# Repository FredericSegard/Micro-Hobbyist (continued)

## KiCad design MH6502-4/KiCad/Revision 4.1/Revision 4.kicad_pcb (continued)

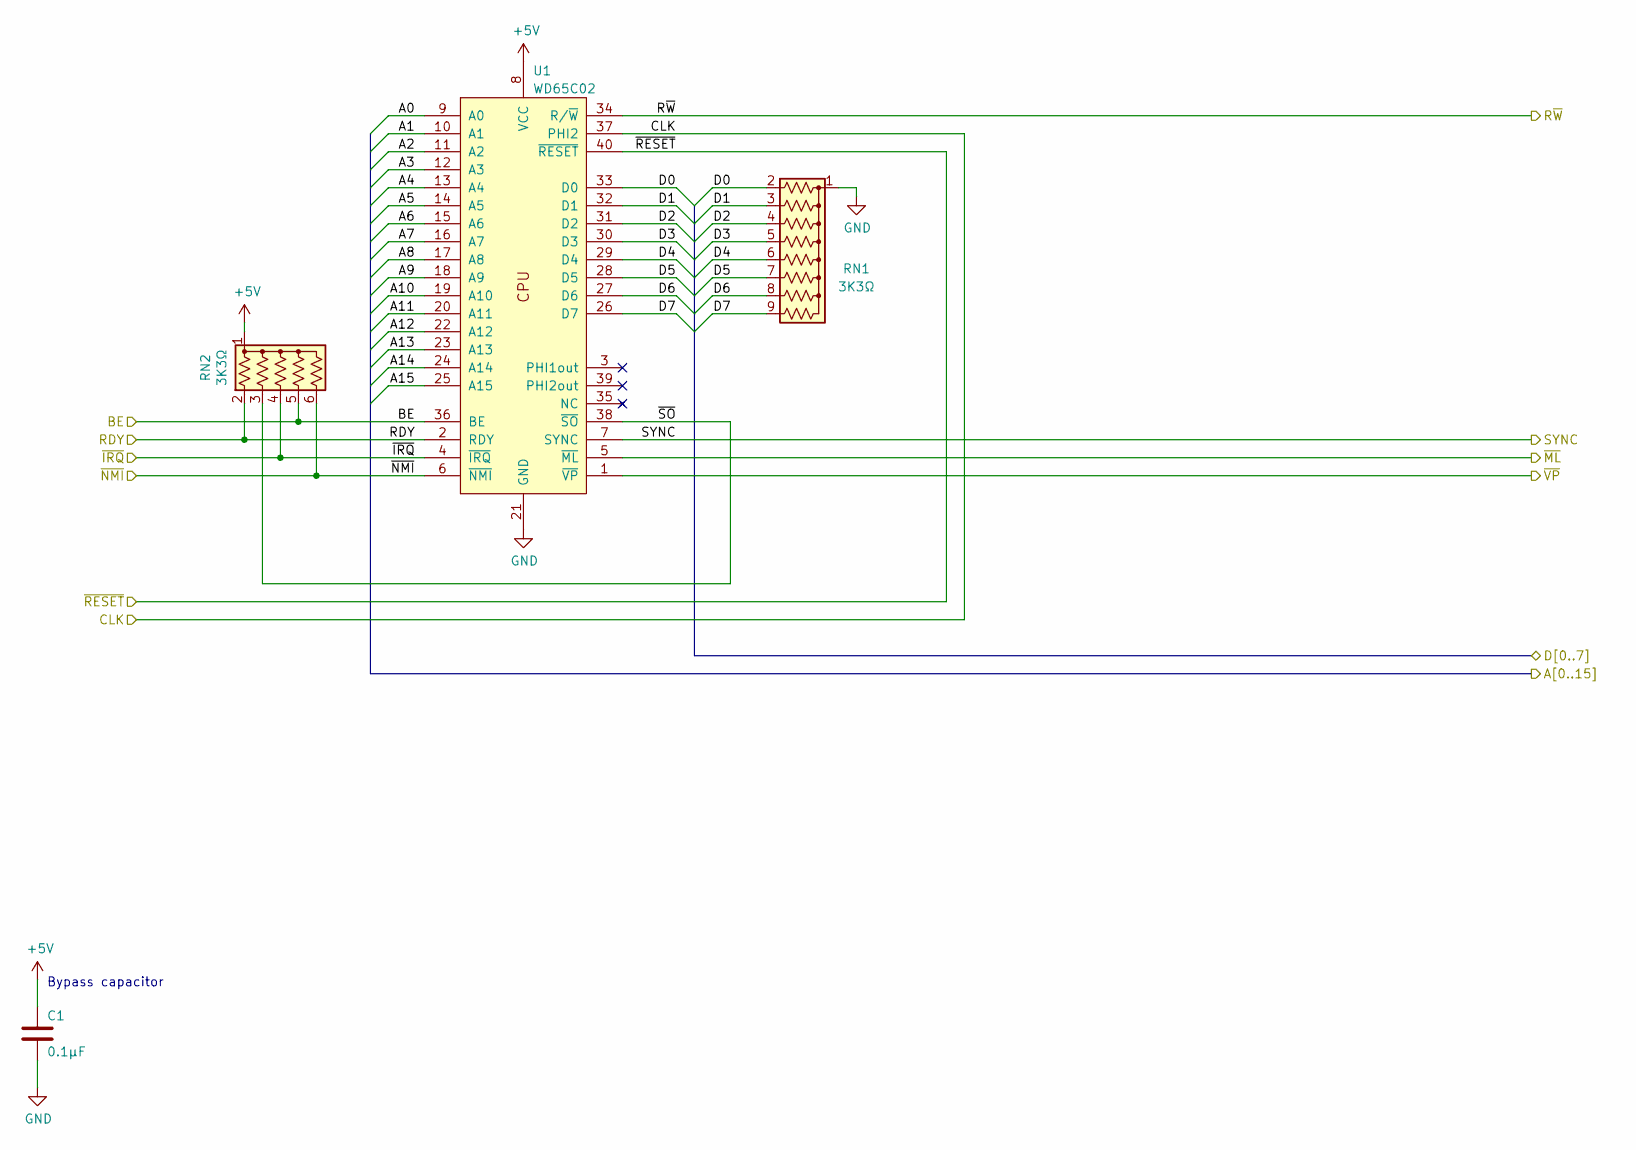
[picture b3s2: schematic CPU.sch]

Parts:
C1: 0.1µF; C_Disc_D3.0mm_W1.6mm_P2.50mm
RN1: 3K3Ω; R_Array_SIP9
RN2: 3K3Ω; R_Array_SIP6
U1: WD65C02; DIP-40_W15.24mm_Socket

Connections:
+5V: C1.1, RN2.1 (common), U1.8 (VCC); also elsewhere on the board
/ACIA/A0: U1.9 (A0); also elsewhere on the board
/ACIA/A1: U1.10 (A1); also elsewhere on the board
/ACIA/D0: RN1.2 (R1), U1.33 (D0); also elsewhere on the board
/ACIA/D1: RN1.3 (R2), U1.32 (D1); also elsewhere on the board
/ACIA/D2: RN1.4 (R3), U1.31 (D2); also elsewhere on the board
/ACIA/D3: RN1.5 (R4), U1.30 (D3); also elsewhere on the board
/ACIA/D4: RN1.6 (R5), U1.29 (D4); also elsewhere on the board
/ACIA/D5: RN1.7 (R6), U1.28 (D5); also elsewhere on the board
/ACIA/D6: RN1.8 (R7), U1.27 (D6); also elsewhere on the board
/ACIA/D7: RN1.9 (R8), U1.26 (D7); also elsewhere on the board
/BE: RN2.5 (R4), U1.36 (BE); also elsewhere on the board
/Bus/A2: U1.11 (A2); also elsewhere on the board
/Bus/A3: U1.12 (A3); also elsewhere on the board
/Bus/A4: U1.13 (A4); also elsewhere on the board
/Bus/A5: U1.14 (A5); also elsewhere on the board
/Bus/A6: U1.15 (A6); also elsewhere on the board
/Bus/A7: U1.16 (A7); also elsewhere on the board
/CLK: U1.37 (PHI2); also elsewhere on the board
/CPU/A8: U1.17 (A8); also elsewhere on the board
/CPU/A9: U1.18 (A9); also elsewhere on the board
/CPU/A10: U1.19 (A10); also elsewhere on the board
/CPU/A11: U1.20 (A11); also elsewhere on the board
/CPU/A12: U1.22 (A12); also elsewhere on the board
/CPU/A13: U1.23 (A13); also elsewhere on the board
/CPU/A14: U1.24 (A14); also elsewhere on the board
/CPU/A15: U1.25 (A15); also elsewhere on the board
/CPU/~SO: RN2.3 (R2), U1.38 (~SO)
/RDY: RN2.2 (R1), U1.2 (RDY); also elsewhere on the board
/R~W: U1.34 (R/~W); also elsewhere on the board
/SYNC: U1.7 (SYNC); also elsewhere on the board
/~IRQ: RN2.4 (R3), U1.4 (~IRQ); also elsewhere on the board
/~ML: U1.5 (~ML); also elsewhere on the board
/~NMI: RN2.6 (R5), U1.6 (~NMI); also elsewhere on the board
/~RESET: U1.40 (~RESET); also elsewhere on the board
/~VP: U1.1 (~VP); also elsewhere on the board
GND: C1.2, RN1.1 (common), U1.21 (GND); also elsewhere on the board

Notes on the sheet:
Bypass capacitor

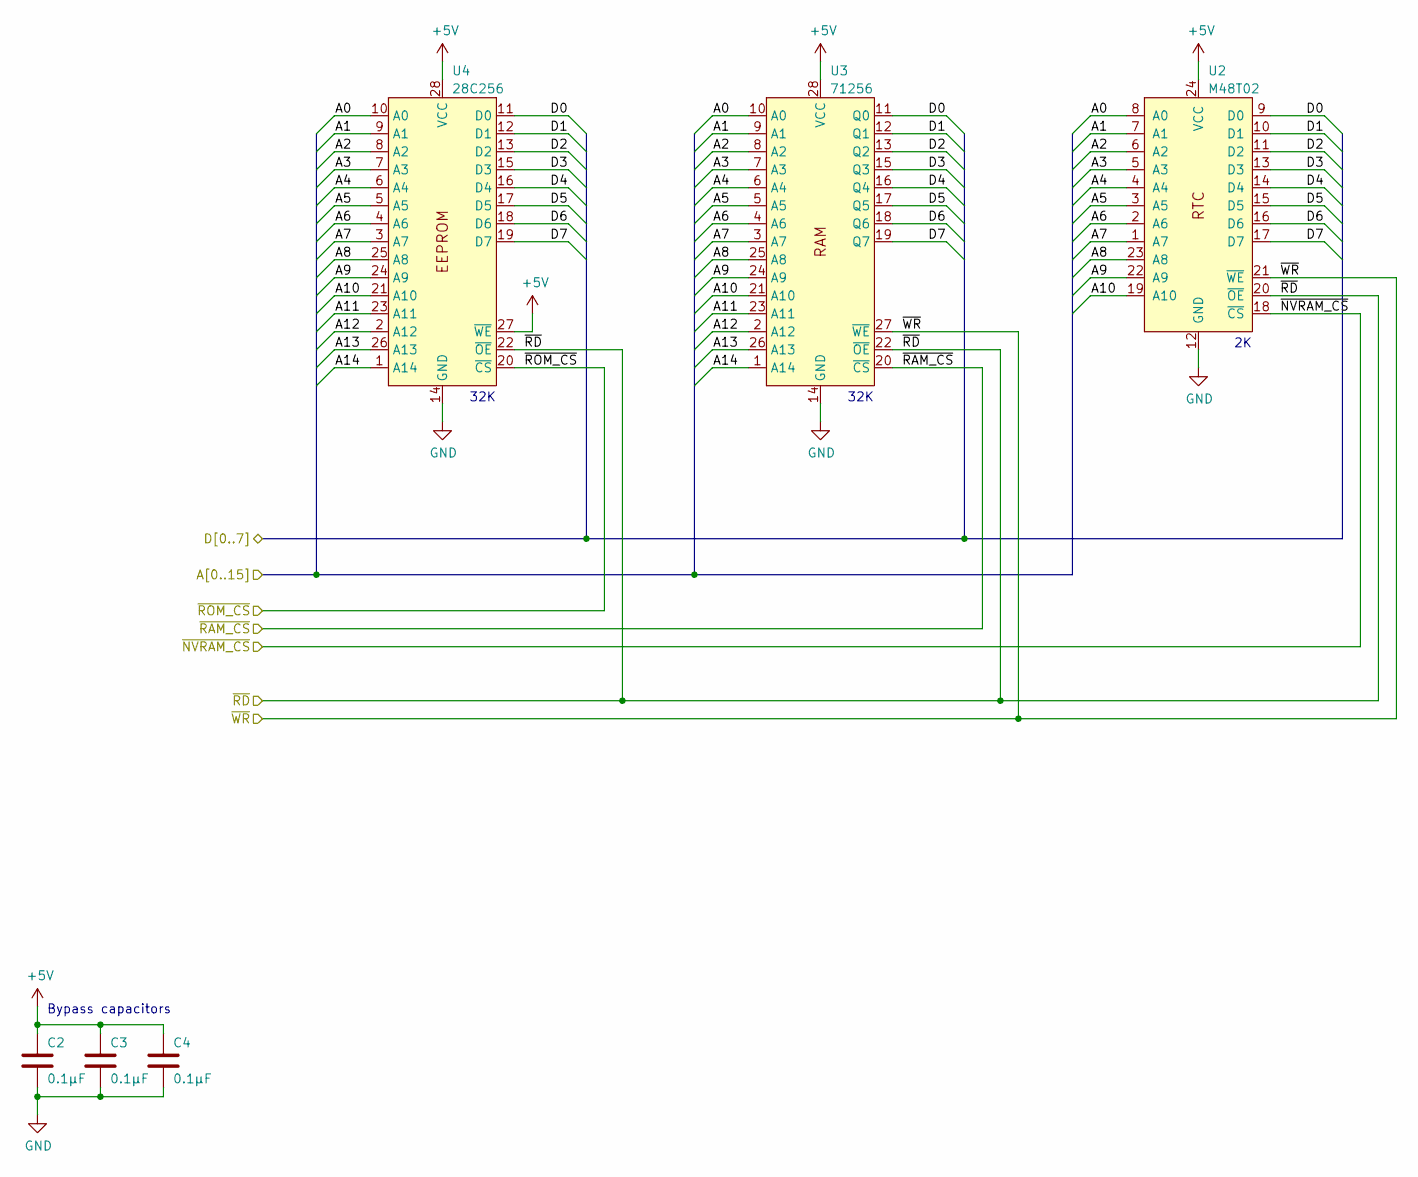
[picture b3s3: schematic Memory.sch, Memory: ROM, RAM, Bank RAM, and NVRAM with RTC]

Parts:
C2, C3, C4: 0.1µF; C_Disc_D3.0mm_W1.6mm_P2.50mm
U2: M48T02; DIP-24_W15.24mm_Socket
U3: 71256; DIP-28_W7.62mm_Socket
U4: 28C256; ZIF-28

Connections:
+5V: C2.1, C3.1, C4.1, U2.24 (VCC), U3.28 (VCC), U4.27 (~WE), U4.28 (VCC); also elsewhere on the board
/ACIA/A0: U2.8 (A0), U3.10 (A0), U4.10 (A0); also elsewhere on the board
/ACIA/A1: U2.7 (A1), U3.9 (A1), U4.9 (A1); also elsewhere on the board
/ACIA/D0: U2.9 (D0), U3.11 (Q0), U4.11 (D0); also elsewhere on the board
/ACIA/D1: U2.10 (D1), U3.12 (Q1), U4.12 (D1); also elsewhere on the board
/ACIA/D2: U2.11 (D2), U3.13 (Q2), U4.13 (D2); also elsewhere on the board
/ACIA/D3: U2.13 (D3), U3.15 (Q3), U4.15 (D3); also elsewhere on the board
/ACIA/D4: U2.14 (D4), U3.16 (Q4), U4.16 (D4); also elsewhere on the board
/ACIA/D5: U2.15 (D5), U3.17 (Q5), U4.17 (D5); also elsewhere on the board
/ACIA/D6: U2.16 (D6), U3.18 (Q6), U4.18 (D6); also elsewhere on the board
/ACIA/D7: U2.17 (D7), U3.19 (Q7), U4.19 (D7); also elsewhere on the board
/Bus/A2: U2.6 (A2), U3.8 (A2), U4.8 (A2); also elsewhere on the board
/Bus/A3: U2.5 (A3), U3.7 (A3), U4.7 (A3); also elsewhere on the board
/Bus/A4: U2.4 (A4), U3.6 (A4), U4.6 (A4); also elsewhere on the board
/Bus/A5: U2.3 (A5), U3.5 (A5), U4.5 (A5); also elsewhere on the board
/Bus/A6: U2.2 (A6), U3.4 (A6), U4.4 (A6); also elsewhere on the board
/Bus/A7: U2.1 (A7), U3.3 (A7), U4.3 (A7); also elsewhere on the board
/CPU/A8: U2.23 (A8), U3.25 (A8), U4.25 (A8); also elsewhere on the board
/CPU/A9: U2.22 (A9), U3.24 (A9), U4.24 (A9); also elsewhere on the board
/CPU/A10: U2.19 (A10), U3.21 (A10), U4.21 (A10); also elsewhere on the board
/CPU/A11: U3.23 (A11), U4.23 (A11); also elsewhere on the board
/CPU/A12: U3.2 (A12), U4.2 (A12); also elsewhere on the board
/CPU/A13: U3.26 (A13), U4.26 (A13); also elsewhere on the board
/CPU/A14: U3.1 (A14), U4.1 (A14); also elsewhere on the board
/~NVRAM: U2.18 (~CS); also elsewhere on the board
/~RAM: U3.20 (~CS); also elsewhere on the board
/~RD: U2.20 (~OE), U3.22 (~OE), U4.22 (~OE); also elsewhere on the board
/~ROM: U4.20 (~CS); also elsewhere on the board
/~WR: U2.21 (~WE), U3.27 (~WE); also elsewhere on the board
GND: C2.2, C3.2, C4.2, U2.12 (GND), U3.14 (GND), U4.14 (GND); also elsewhere on the board

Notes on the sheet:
32K
Bypass capacitors

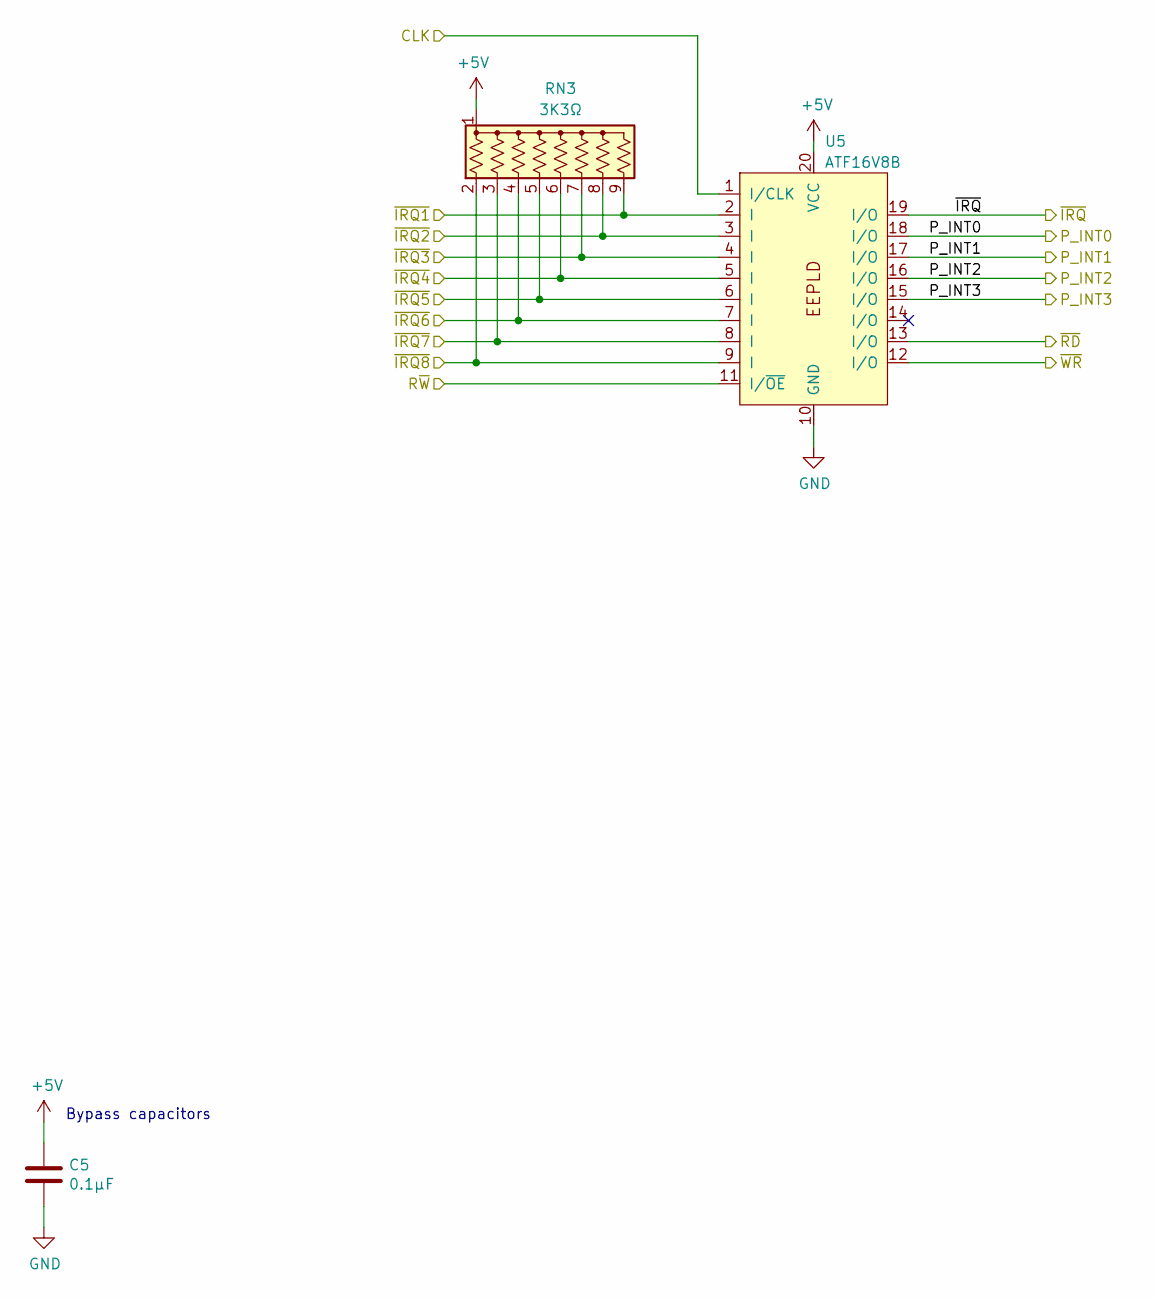
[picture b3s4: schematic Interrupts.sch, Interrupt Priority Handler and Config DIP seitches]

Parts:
C5: 0.1µF; C_Disc_D3.0mm_W1.6mm_P2.50mm
RN3: 3K3Ω; R_Array_SIP9
U5: ATF16V8B; DIP-20_W7.62mm_Socket

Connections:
+5V: C5.1, RN3.1 (common), U5.20 (VCC); also elsewhere on the board
/CLK: U5.1 (I/CLK); also elsewhere on the board
/P_INT0: U5.18 (I/O); also elsewhere on the board
/P_INT1: U5.17 (I/O); also elsewhere on the board
/P_INT2: U5.16 (I/O); also elsewhere on the board
/P_INT3: U5.15 (I/O); also elsewhere on the board
/R~W: U5.11 (I/~OE); also elsewhere on the board
/~IRQ: U5.19 (I/O); also elsewhere on the board
/~IRQ1: RN3.9 (R8), U5.2 (I); also elsewhere on the board
/~IRQ2: RN3.8 (R7), U5.3 (I); also elsewhere on the board
/~IRQ3: RN3.7 (R6), U5.4 (I); also elsewhere on the board
/~IRQ4: RN3.6 (R5), U5.5 (I); also elsewhere on the board
/~IRQ5: RN3.5 (R4), U5.6 (I); also elsewhere on the board
/~IRQ6: RN3.4 (R3), U5.7 (I); also elsewhere on the board
/~IRQ7: RN3.3 (R2), U5.8 (I); also elsewhere on the board
/~IRQ8: RN3.2 (R1), U5.9 (I)
/~RD: U5.13 (I/O); also elsewhere on the board
/~WR: U5.12 (I/O); also elsewhere on the board
GND: C5.2, U5.10 (GND); also elsewhere on the board

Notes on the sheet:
Bypass capacitors

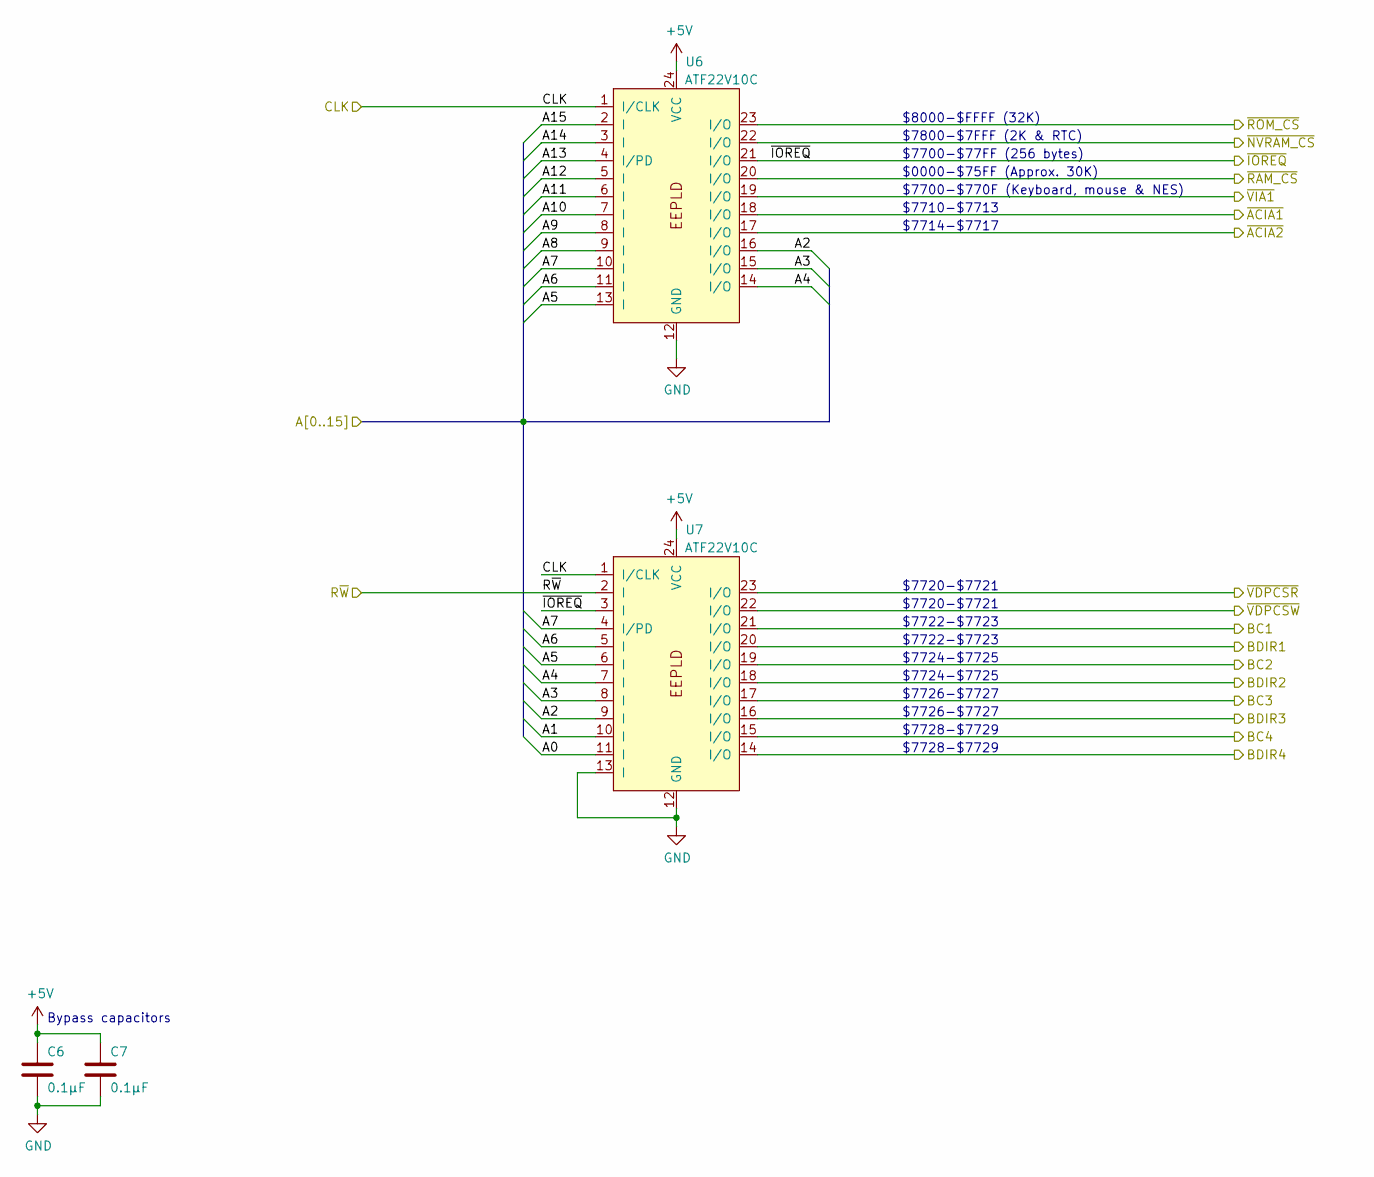
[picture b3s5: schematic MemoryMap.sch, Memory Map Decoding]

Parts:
C6, C7: 0.1µF; C_Disc_D3.0mm_W1.6mm_P2.50mm
U6, U7: ATF22V10C; DIP-24_W7.62mm_Socket

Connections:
+5V: C6.1, C7.1, U6.24 (VCC), U7.24 (VCC); also elsewhere on the board
/ACIA/A0: U7.11 (I); also elsewhere on the board
/ACIA/A1: U7.10 (I); also elsewhere on the board
/BC1: U7.21 (I/O); also elsewhere on the board
/BC2: U7.19 (I/O); also elsewhere on the board
/BC3: U7.17 (I/O); also elsewhere on the board
/BC4: U7.15 (I/O); also elsewhere on the board
/BDIR1: U7.20 (I/O); also elsewhere on the board
/BDIR2: U7.18 (I/O); also elsewhere on the board
/BDIR3: U7.16 (I/O); also elsewhere on the board
/BDIR4: U7.14 (I/O); also elsewhere on the board
/Bus/A2: U6.16 (I/O), U7.9 (I); also elsewhere on the board
/Bus/A3: U6.15 (I/O), U7.8 (I); also elsewhere on the board
/Bus/A4: U6.14 (I/O), U7.7 (I); also elsewhere on the board
/Bus/A5: U6.13 (I), U7.6 (I); also elsewhere on the board
/Bus/A6: U6.11 (I), U7.5 (I); also elsewhere on the board
/Bus/A7: U6.10 (I), U7.4 (I/PD); also elsewhere on the board
/CLK: U6.1 (I/CLK), U7.1 (I/CLK); also elsewhere on the board
/CPU/A8: U6.9 (I); also elsewhere on the board
/CPU/A9: U6.8 (I); also elsewhere on the board
/CPU/A10: U6.7 (I); also elsewhere on the board
/CPU/A11: U6.6 (I); also elsewhere on the board
/CPU/A12: U6.5 (I); also elsewhere on the board
/CPU/A13: U6.4 (I/PD); also elsewhere on the board
/CPU/A14: U6.3 (I); also elsewhere on the board
/CPU/A15: U6.2 (I); also elsewhere on the board
/R~W: U7.2 (I); also elsewhere on the board
/~ACIA1: U6.18 (I/O); also elsewhere on the board
/~ACIA2: U6.17 (I/O); also elsewhere on the board
/~IOREQ: U6.21 (I/O), U7.3 (I); also elsewhere on the board
/~NVRAM: U6.22 (I/O); also elsewhere on the board
/~RAM: U6.20 (I/O); also elsewhere on the board
/~ROM: U6.23 (I/O); also elsewhere on the board
/~VDPCSR: U7.23 (I/O); also elsewhere on the board
/~VDPCSW: U7.22 (I/O); also elsewhere on the board
/~VIA1: U6.19 (I/O); also elsewhere on the board
GND: C6.2, C7.2, U6.12 (GND), U7.12 (GND), U7.13 (I); also elsewhere on the board

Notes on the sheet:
Bypass capacitors
$8000-$FFFF (32K)
$7800-$7FFF (2K & RTC)
$7700-$77FF (256 bytes)
$0000-$75FF (Approx. 30K)
$7714-$7717
$7700-$770F (Keyboard, mouse & NES)
$7720-$7721
$7722-$7723
$7724-$7725
$7726-$7727
$7710-$7713
$7728-$7729

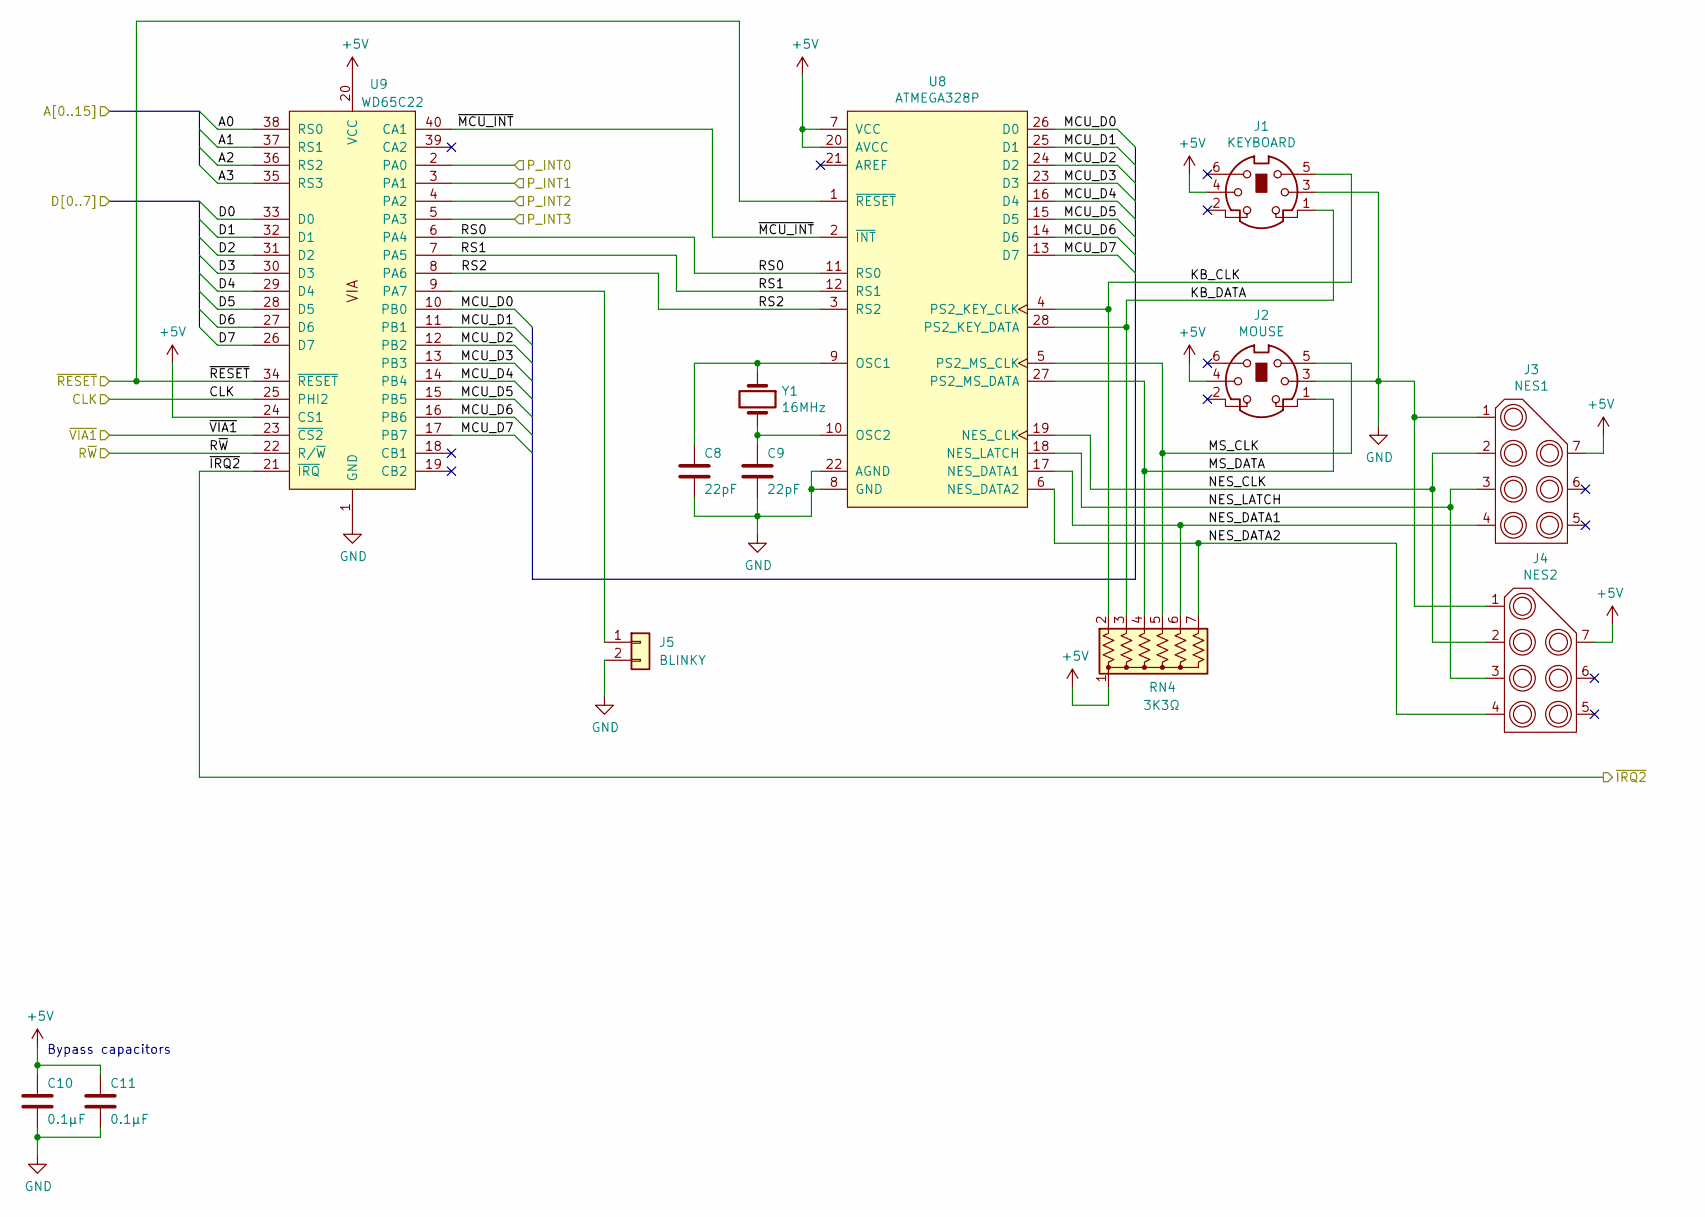
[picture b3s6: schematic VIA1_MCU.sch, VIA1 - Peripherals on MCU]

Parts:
C8, C9: 22pF; C_Disc_D3.0mm_W1.6mm_P2.50mm
C10, C11: 0.1µF; C_Disc_D3.0mm_W1.6mm_P2.50mm
J1: KEYBOARD; Mini-DIN_6p
J2: MOUSE; Mini-DIN_6p
J3: NES1; NES_Connector
J4: NES2; NES_Connector
J5: BLINKY; PinHeader_1x02_P2.54mm_Vertical
RN4: 3K3Ω; R_Array_SIP7
U8: ATMEGA328P; DIP-28_W7.62mm_Socket
U9: WD65C22; DIP-40_W15.24mm_Socket
Y1: 16MHz; Crystal_HC18-U_Vertical

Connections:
+5V: C10.1, C11.1, J1.4, J2.4, J3.7, J4.7, RN4.1 (common), U8.7 (VCC), U8.20 (AVCC), U9.20 (VCC), U9.24 (CS1); also elsewhere on the board
/ACIA/A0: U9.38 (RS0); also elsewhere on the board
/ACIA/A1: U9.37 (RS1); also elsewhere on the board
/ACIA/D0: U9.33 (D0); also elsewhere on the board
/ACIA/D1: U9.32 (D1); also elsewhere on the board
/ACIA/D2: U9.31 (D2); also elsewhere on the board
/ACIA/D3: U9.30 (D3); also elsewhere on the board
/ACIA/D4: U9.29 (D4); also elsewhere on the board
/ACIA/D5: U9.28 (D5); also elsewhere on the board
/ACIA/D6: U9.27 (D6); also elsewhere on the board
/ACIA/D7: U9.26 (D7); also elsewhere on the board
/Bus/A2: U9.36 (RS2); also elsewhere on the board
/Bus/A3: U9.35 (RS3); also elsewhere on the board
/CLK: U9.25 (PHI2); also elsewhere on the board
/P_INT0: U9.2 (PA0); also elsewhere on the board
/P_INT1: U9.3 (PA1); also elsewhere on the board
/P_INT2: U9.4 (PA2); also elsewhere on the board
/P_INT3: U9.5 (PA3); also elsewhere on the board
/R~W: U9.22 (R/~W); also elsewhere on the board
/VIA - Peripherals/KB_CLK: J1.5, RN4.2 (R1), U8.4 (PS2_KEY_CLK)
/VIA - Peripherals/KB_DATA: J1.1, RN4.3 (R2), U8.28 (PS2_KEY_DATA)
/VIA - Peripherals/MCU_D0: U8.26 (D0), U9.10 (PB0)
/VIA - Peripherals/MCU_D1: U8.25 (D1), U9.11 (PB1)
/VIA - Peripherals/MCU_D2: U8.24 (D2), U9.12 (PB2)
/VIA - Peripherals/MCU_D3: U8.23 (D3), U9.13 (PB3)
/VIA - Peripherals/MCU_D4: U8.16 (D4), U9.14 (PB4)
/VIA - Peripherals/MCU_D5: U8.15 (D5), U9.15 (PB5)
/VIA - Peripherals/MCU_D6: U8.14 (D6), U9.16 (PB6)
/VIA - Peripherals/MCU_D7: U8.13 (D7), U9.17 (PB7)
/VIA - Peripherals/MS_CLK: J2.5, RN4.5 (R4), U8.5 (PS2_MS_CLK)
/VIA - Peripherals/MS_DATA: J2.1, RN4.4 (R3), U8.27 (PS2_MS_DATA)
/VIA - Peripherals/NES_CLK: J3.2, J4.2, U8.19 (NES_CLK)
/VIA - Peripherals/NES_DATA1: J3.4, RN4.6 (R5), U8.17 (NES_DATA1)
/VIA - Peripherals/NES_DATA2: J4.4, RN4.7 (R6), U8.6 (NES_DATA2)
/VIA - Peripherals/NES_LATCH: J3.3, J4.3, U8.18 (NES_LATCH)
/VIA - Peripherals/RS0: U8.11 (RS0), U9.6 (PA4)
/VIA - Peripherals/RS1: U8.12 (RS1), U9.7 (PA5)
/VIA - Peripherals/RS2: U8.3 (RS2), U9.8 (PA6)
/VIA - Peripherals/~MCU_INT: U8.2 (~INT), U9.40 (CA1)
/~IRQ2: U9.21 (~IRQ); also elsewhere on the board
/~RESET: U8.1 (~RESET), U9.34 (~RESET); also elsewhere on the board
/~VIA1: U9.23 (~CS2); also elsewhere on the board
GND: C8.2, C9.2, C10.2, C11.2, J1.3, J2.3, J3.1, J4.1, J5.2, U8.8 (GND), U8.22 (AGND), U9.1 (GND); also elsewhere on the board
unnamed: C8.1, U8.9 (OSC1), Y1.1
unnamed: C9.1, U8.10 (OSC2), Y1.2
unnamed: J5.1, U9.9 (PA7)

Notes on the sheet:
Bypass capacitors

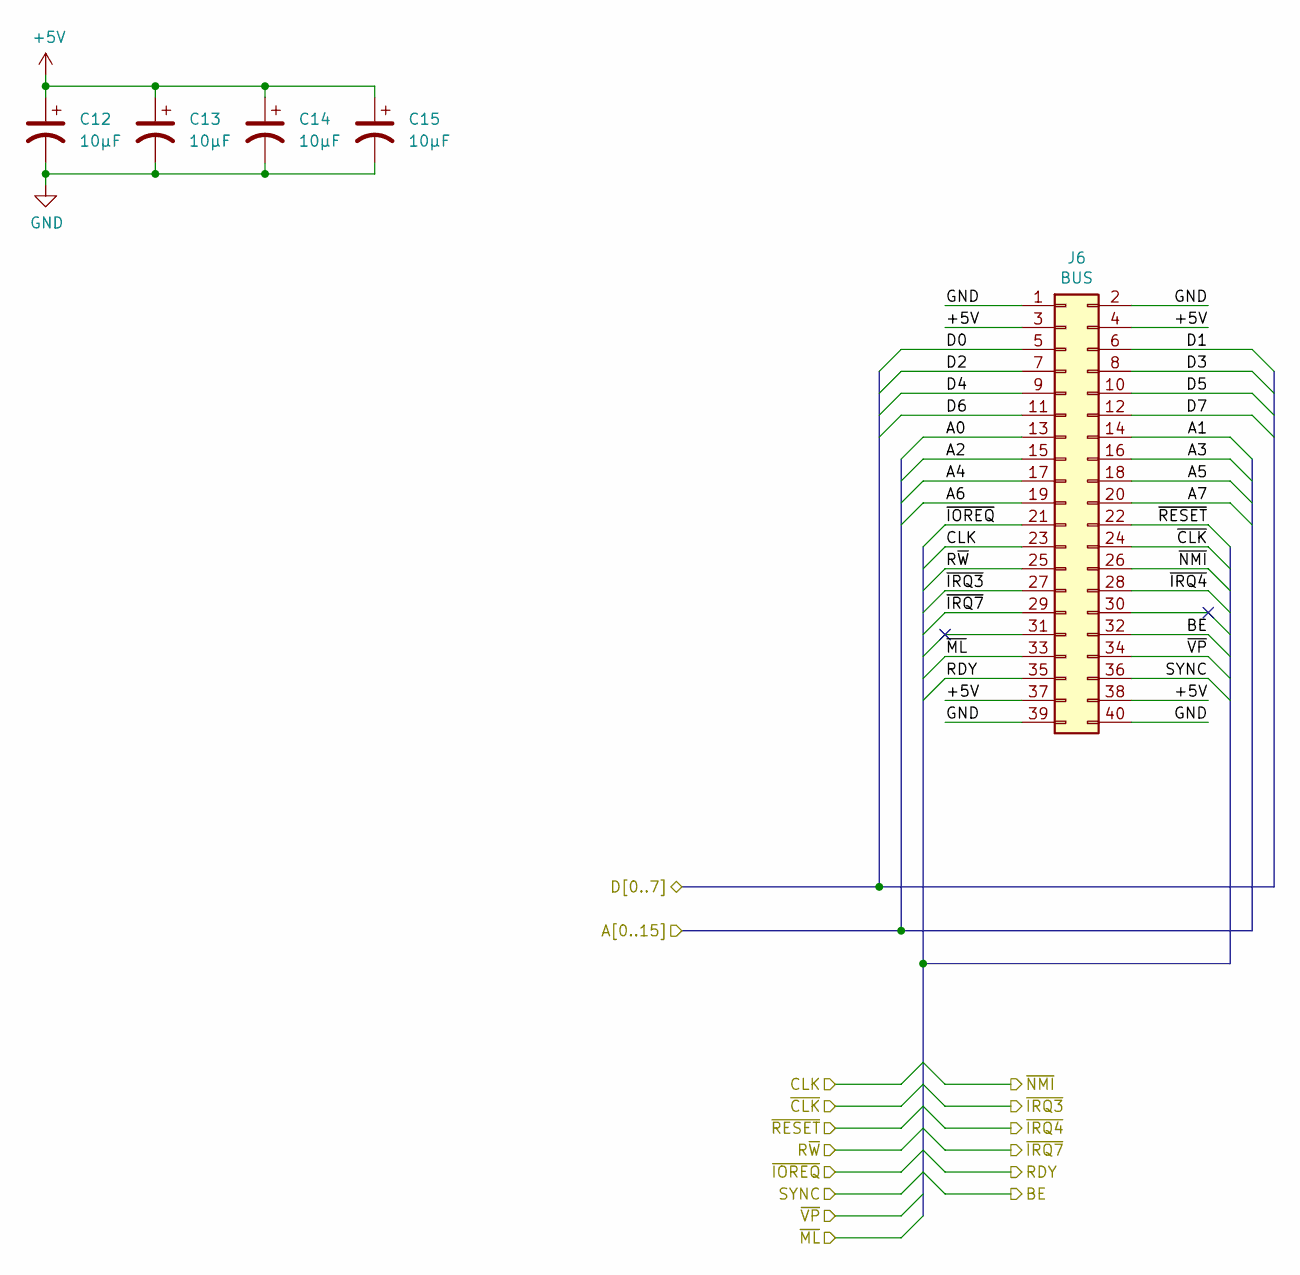
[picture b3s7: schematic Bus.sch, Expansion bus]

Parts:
C12, C13, C14, C15: 10µF; CP_Radial_D6.3mm_P2.50mm
J6: BUS; PinHeader_2x20_P2.54mm_Vertical

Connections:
+5V: C12.1, C13.1, C14.1, C15.1, J6.3, J6.4, J6.37, J6.38; also elsewhere on the board
/ACIA/A0: J6.13; also elsewhere on the board
/ACIA/A1: J6.14; also elsewhere on the board
/ACIA/D0: J6.5; also elsewhere on the board
/ACIA/D1: J6.6; also elsewhere on the board
/ACIA/D2: J6.7; also elsewhere on the board
/ACIA/D3: J6.8; also elsewhere on the board
/ACIA/D4: J6.9; also elsewhere on the board
/ACIA/D5: J6.10; also elsewhere on the board
/ACIA/D6: J6.11; also elsewhere on the board
/ACIA/D7: J6.12; also elsewhere on the board
/BE: J6.32; also elsewhere on the board
/Bus/A2: J6.15; also elsewhere on the board
/Bus/A3: J6.16; also elsewhere on the board
/Bus/A4: J6.17; also elsewhere on the board
/Bus/A5: J6.18; also elsewhere on the board
/Bus/A6: J6.19; also elsewhere on the board
/Bus/A7: J6.20; also elsewhere on the board
/CLK: J6.23; also elsewhere on the board
/RDY: J6.35; also elsewhere on the board
/R~W: J6.25; also elsewhere on the board
/SYNC: J6.36; also elsewhere on the board
/~CLK: J6.24; also elsewhere on the board
/~IOREQ: J6.21; also elsewhere on the board
/~IRQ3: J6.27; also elsewhere on the board
/~IRQ4: J6.28; also elsewhere on the board
/~IRQ7: J6.29; also elsewhere on the board
/~ML: J6.33; also elsewhere on the board
/~NMI: J6.26; also elsewhere on the board
/~RESET: J6.22; also elsewhere on the board
/~VP: J6.34; also elsewhere on the board
GND: C12.2, C13.2, C14.2, C15.2, J6.1, J6.2, J6.39, J6.40; also elsewhere on the board

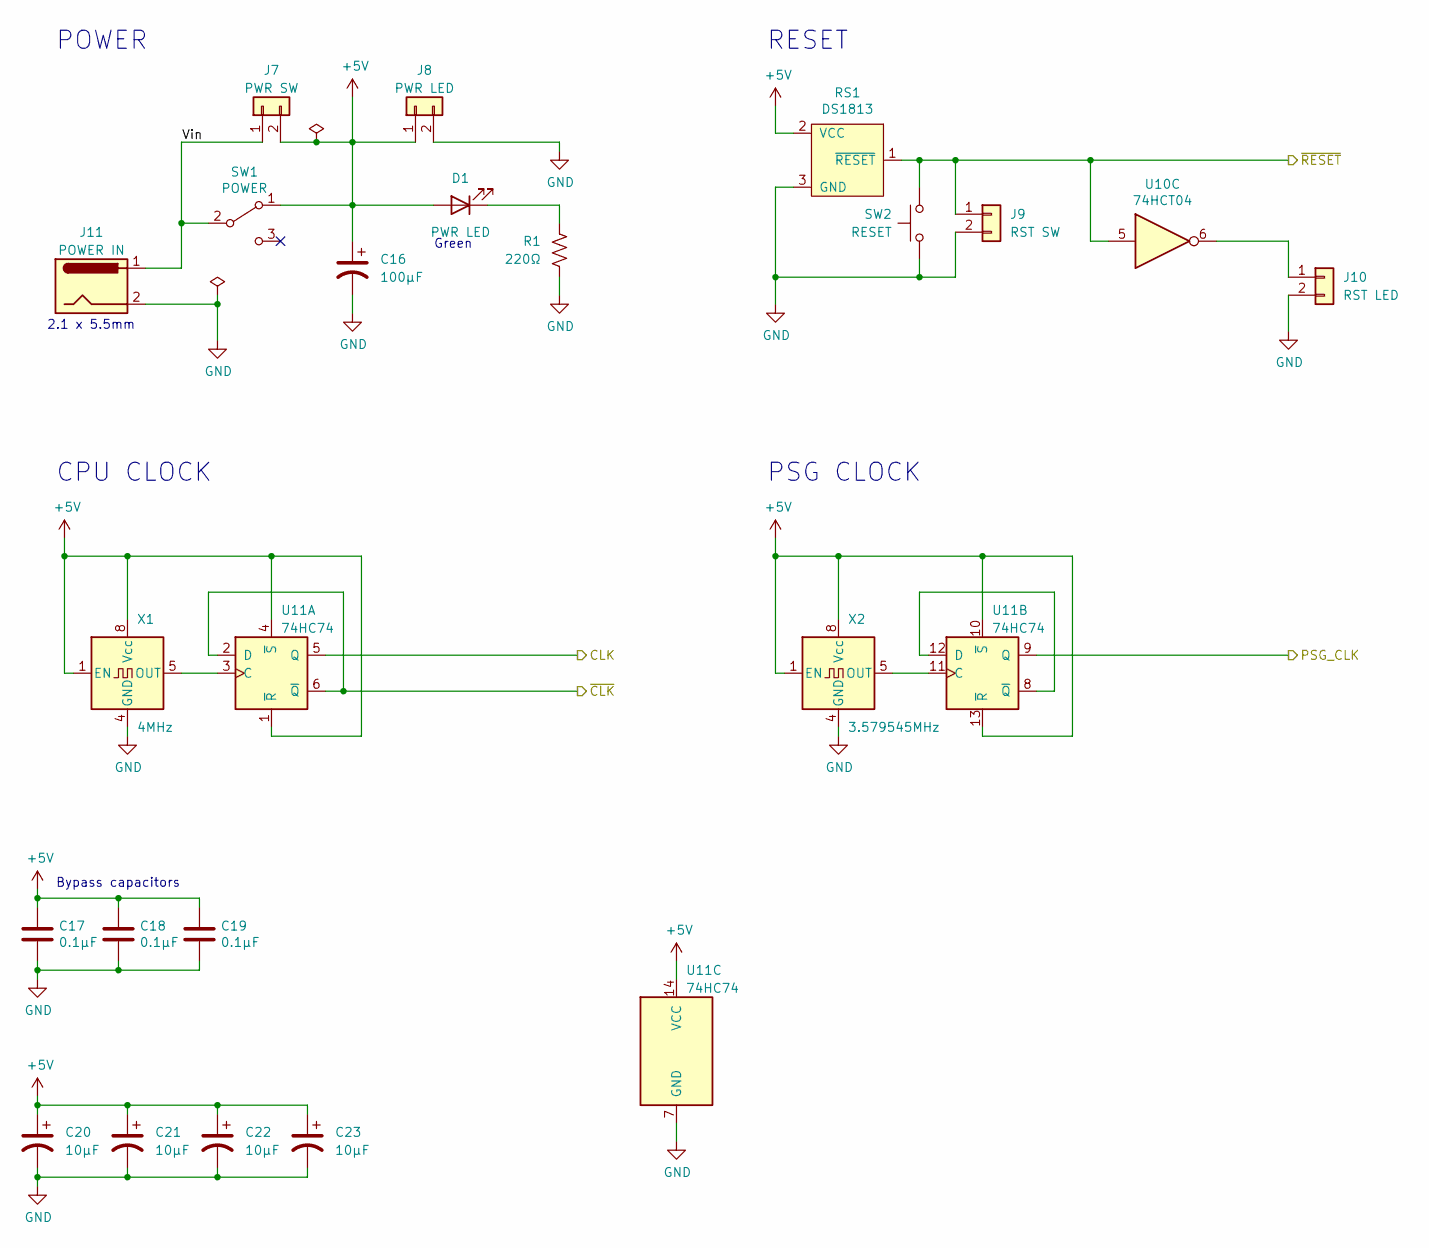
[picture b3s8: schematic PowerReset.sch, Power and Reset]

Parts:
C16: 100µF; CP_Radial_D8.0mm_P3.80mm
C17, C18, C19: 0.1µF; C_Disc_D3.0mm_W1.6mm_P2.50mm
C20, C21, C22, C23: 10µF; CP_Radial_D6.3mm_P2.50mm
D1: PWR LED; LED_D3.0mm
J7: PWR SW; PinHeader_1x02_P2.54mm_Vertical
J8: PWR LED; PinHeader_1x02_P2.54mm_Vertical
J9: RST SW; PinHeader_1x02_P2.54mm_Vertical
J10: RST LED; PinHeader_1x02_P2.54mm_Vertical
J11: POWER IN; BarrelJack_Horizontal
R1: 220Ω; R_Axial_DIN0207_L6.3mm_D2.5mm_P10.16mm_Horizontal
RS1: DS1813; TO-92L_Inline_Wide
SW1: POWER; Microswitch_3mm_spacing_2
SW2: RESET; SW_PUSH_6mm
U10: 74HCT04; DIP-14_W7.62mm_Socket
U11: 74HC74; DIP-14_W7.62mm_Socket
X1: 4MHz; Oscillator_DIP-8
X2: 3.579545MHz; Oscillator_DIP-8

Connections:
+5V: C16.1, C17.1, C18.1, C19.1, C20.1, C21.1, C22.1, C23.1, D1.2 (A), J7.2, J8.1, RS1.2 (VCC), SW1.1 (A), U11.1 (~R), U11.4 (~S), U11.10 (~S), U11.13 (~R), U11.14 (VCC), X1.1 (EN), X1.8 (Vcc), X2.1 (EN), X2.8 (Vcc); also elsewhere on the board
/CLK: U11.5 (Q); also elsewhere on the board
/PSG_CLK: U11.9 (Q); also elsewhere on the board
/Power, Reset & Clock/Vin: J7.1, J11.1, SW1.2 (B)
/~CLK: U11.2 (D), U11.6 (~Q); also elsewhere on the board
/~RESET: J9.1, RS1.1 (~RESET), SW2.1, U10.5; also elsewhere on the board
GND: C16.2, C17.2, C18.2, C19.2, C20.2, C21.2, C22.2, C23.2, J8.2, J9.2, J10.2, J11.2, R1.1, RS1.3 (GND), SW2.2, U11.7 (GND), X1.4 (GND), X2.4 (GND); also elsewhere on the board
unnamed: D1.1 (K), R1.2
unnamed: J10.1, U10.6
unnamed: U11.3 (C), X1.5 (OUT)
unnamed: U11.11 (C), X2.5 (OUT)
unnamed: U11.8 (~Q), U11.12 (D)

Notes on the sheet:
2.1 x 5.5mm
Green
Bypass capacitors
POWER
CPU CLOCK
RESET
PSG CLOCK

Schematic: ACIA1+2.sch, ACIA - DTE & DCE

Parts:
C24, C25, C26, C27, C28, C29, C30, C31: 1µF; C_Disc_D3.0mm_W1.6mm_P2.50mm
C32, C33, C34, C35, C36: 0.1µF; C_Disc_D3.0mm_W1.6mm_P2.50mm
J12: DCE-F; DSUB-9_Female_Horizontal_P2.77x2.84mm_EdgePinOffset7.70mm_H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
J13: CTS; PinHeader_1x02_P2.54mm_Vertical
J14: RX; PinHeader_1x02_P2.54mm_Vertical
J15: SERIAL TTL; Mini-DIN_6p
J16: DTE-M; DSUB-9_Male_Horizontal_P2.77x2.84mm_EdgePinOffset7.70mm_Hou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
J17: SERIAL TTL; PinHeader_1x06_P2.54mm_Vertical
U12, U14: R65C51P2; DIP-28_W15.24mm_Socket
U13, U15: MAX232; DIP-16_W7.62mm_Socket
X3: 1.8432MHz; Oscillator_DIP-8

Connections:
+5V: C24.2, C28.2, C32.1, C33.1, C34.1, C35.1, C36.1, J15.4, J17.3, U12.2 (CS0), U12.15 (VCC), U13.16 (VCC), U14.2 (CS0), U14.15 (VCC), U15.16 (VCC), X3.1 (EN), X3.8 (Vcc); also elsewhere on the board
/ACIA/A0: U12.13 (RS0), U14.13 (RS0); also elsewhere on the board
/ACIA/A1: U12.14 (RS1), U14.14 (RS1); also elsewhere on the board
/ACIA/ACLK: U12.6 (XTLI), U14.6 (XTLI), X3.5 (OUT)
/ACIA/CTS: J13.1, J15.5, J17.2, U14.9 (~CTS)
/ACIA/D0: U12.18 (D0), U14.18 (D0); also elsewhere on the board
/ACIA/D1: U12.19 (D1), U14.19 (D1); also elsewhere on the board
/ACIA/D2: U12.20 (D2), U14.20 (D2); also elsewhere on the board
/ACIA/D3: U12.21 (D3), U14.21 (D3); also elsewhere on the board
/ACIA/D4: U12.22 (D4), U14.22 (D4); also elsewhere on the board
/ACIA/D5: U12.23 (D5), U14.23 (D5); also elsewhere on the board
/ACIA/D6: U12.24 (D6), U14.24 (D6); also elsewhere on the board
/ACIA/D7: U12.25 (D7), U14.25 (D7); also elsewhere on the board
/ACIA/RTS: J15.6, J17.6, U14.8 (~RTS), U15.10 (T2IN)
/ACIA/RX: J14.1, J15.1, J17.5, U14.12 (Rx_Data)
/ACIA/TX: J15.2, J17.4, U14.10 (Tx_Data), U15.11 (T1IN)
/CLK: U12.27 (PHI2), U14.27 (PHI2); also elsewhere on the board
/R~W: U12.28 (R/~W), U14.28 (R/~W); also elsewhere on the board
/~ACIA1: U12.3 (~CS1); also elsewhere on the board
/~ACIA2: U14.3 (~CS1); also elsewhere on the board
/~IRQ5: U12.26 (~IRQ); also elsewhere on the board
/~IRQ6: U14.26 (~IRQ); also elsewhere on the board
/~RESET: U12.4 (~RESET), U14.4 (~RESET); also elsewhere on the board
GND: C27.1, C31.1, C32.2, C33.2, C34.2, C35.2, C36.2, J12.5, J15.3, J16.5, J17.1, U12.1 (GND), U12.16 (~DCD), U12.17 (~DSR), U13.15 (GND), U14.1 (GND), U14.16 (~DCD), U14.17 (~DSR), U15.15 (GND), X3.4 (GND); also elsewhere on the board
unnamed: C24.1, U13.2 (VS+)
unnamed: C25.1, U13.1 (C1+)
unnamed: C25.2, U13.3 (C1-)
unnamed: C26.1, U13.4 (C2+)
unnamed: C26.2, U13.5 (C2-)
unnamed: C27.2, U13.6 (VS-)
unnamed: C28.1, U15.2 (VS+)
unnamed: C29.1, U15.1 (C1+)
unnamed: C29.2, U15.3 (C1-)
unnamed: C30.1, U15.4 (C2+)
unnamed: C30.2, U15.5 (C2-)
unnamed: C31.2, U15.6 (VS-)
unnamed: J12.2, U13.14 (T1OUT)
unnamed: J12.3, U13.13 (R1IN)
unnamed: J12.7, U13.8 (R2IN)
unnamed: J12.8, U13.7 (T2OUT)
unnamed: J13.2, U15.9 (R2OUT)
unnamed: J14.2, U15.12 (R1OUT)
unnamed: J16.2, U15.13 (R1IN)
unnamed: J16.3, U15.14 (T1OUT)
unnamed: J16.7, U15.7 (T2OUT)
unnamed: J16.8, U15.8 (R2IN)
unnamed: U12.8 (~RTS), U13.10 (T2IN)
unnamed: U12.9 (~CTS), U13.9 (R2OUT)
unnamed: U12.10 (Tx_Data), U13.11 (T1IN)
unnamed: U12.12 (Rx_Data), U13.12 (R1OUT)

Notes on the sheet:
RTS
CTS
DCE to Computer
DTE to Peripheral
Bypass capacitors
